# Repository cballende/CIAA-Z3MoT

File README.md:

# CIAA-Z3MoT
Simplificación de base board Silabs subGHz :
EZR32 Happy gecko board for QFP48 parts (EZR32HG)
[SLWSTK6244A](https://www.silabs.com/products/development-tools/wireless/proprietary/slwstk6244a-ezr32-happy-gecko-169-mhz-starter-kit)

| Kit        | Frequency(MHz)| Output Power(dBm) |Included Device |
| ------------- |:-------------:| -----:|-----:|
| SLWSTK6244A     | 169 | +20 | ZR32HG330FG63G |

#### Caracteristicas

* Adaptación de [CIAA-Z3R0](http://www.proyecto-ciaa.com.ar/devwiki/doku.php?id=desarrollo:ciaa-z3r0) hacia un enfoque de [MoTe](https://en.wikipedia.org/wiki/Sensor_node).

* Los pines entre Z3R0 y Z3MoT són compatibles en cierto grado, con excepción de los destinados a la interface RF.

* Puertos y pines deprecados de la versión Z3RO a la Z3MoT:
  - A:2,8,9,10. 
  - C:0,1,2,3,4. 

* Introduce 4 GPIO: 
Se utilizan 3 lineas para configurar puerto I2C para memoria EEPROM y posibles MEMs(disponibles V2.0,temperatura,humedad,7DOF,Altímetro-barómetro,luxómetro)

Deja un GPIO libre configurable sobre los restantes puertos:
- A:0,1.
- B:7,8,11,13,14.
- C:8,9,10,14,15.
- D:4,5,6,7.
- E:10,11,12,13.
- F:0,1,2,3,4.

* USB:
El conector usb se modifico, no se utiliza conector soldable. Se implemento un plug en pcb USB A troquelable, brindando la posiblidad soldar tira de pines de paso 1,27" o soldar en PCB tipo castellated.

* Alimentación:
Selección mediante jumper permitiendo conmutar bateria o (USB / PCBtarget).
La alimentación mediante bateria se implemento con fuente DC/DC tipo boost.

* Autonomía:
El stick Z3MoT tiene la posiblidad de usar baterias tipo boton CR2032(3V)(1,8 años autonomia 225 mAh) o mediante Pila AAA(7,25 años 1,5V de 900-1155 mAh). 

* Conectores RF:
Es posible utilizar dos tipos de conectores uno SMD(por defecto) y otro SMA(soldando via).

* JTAG:
Los pines utilizados en Z3RO son los mismos que para Z3MoT. Se adiciona tira de pines para conexión ordenada de JTAG  mediante sondas con resortes montadas sobre una pinza o base con balancin.

#### Schematic

[Schematic in pdf](ciaa-z3mot.pdf)

#### 3D view

## Vista con opciones de bateria y conector RF

## Video (YOUTUBE)

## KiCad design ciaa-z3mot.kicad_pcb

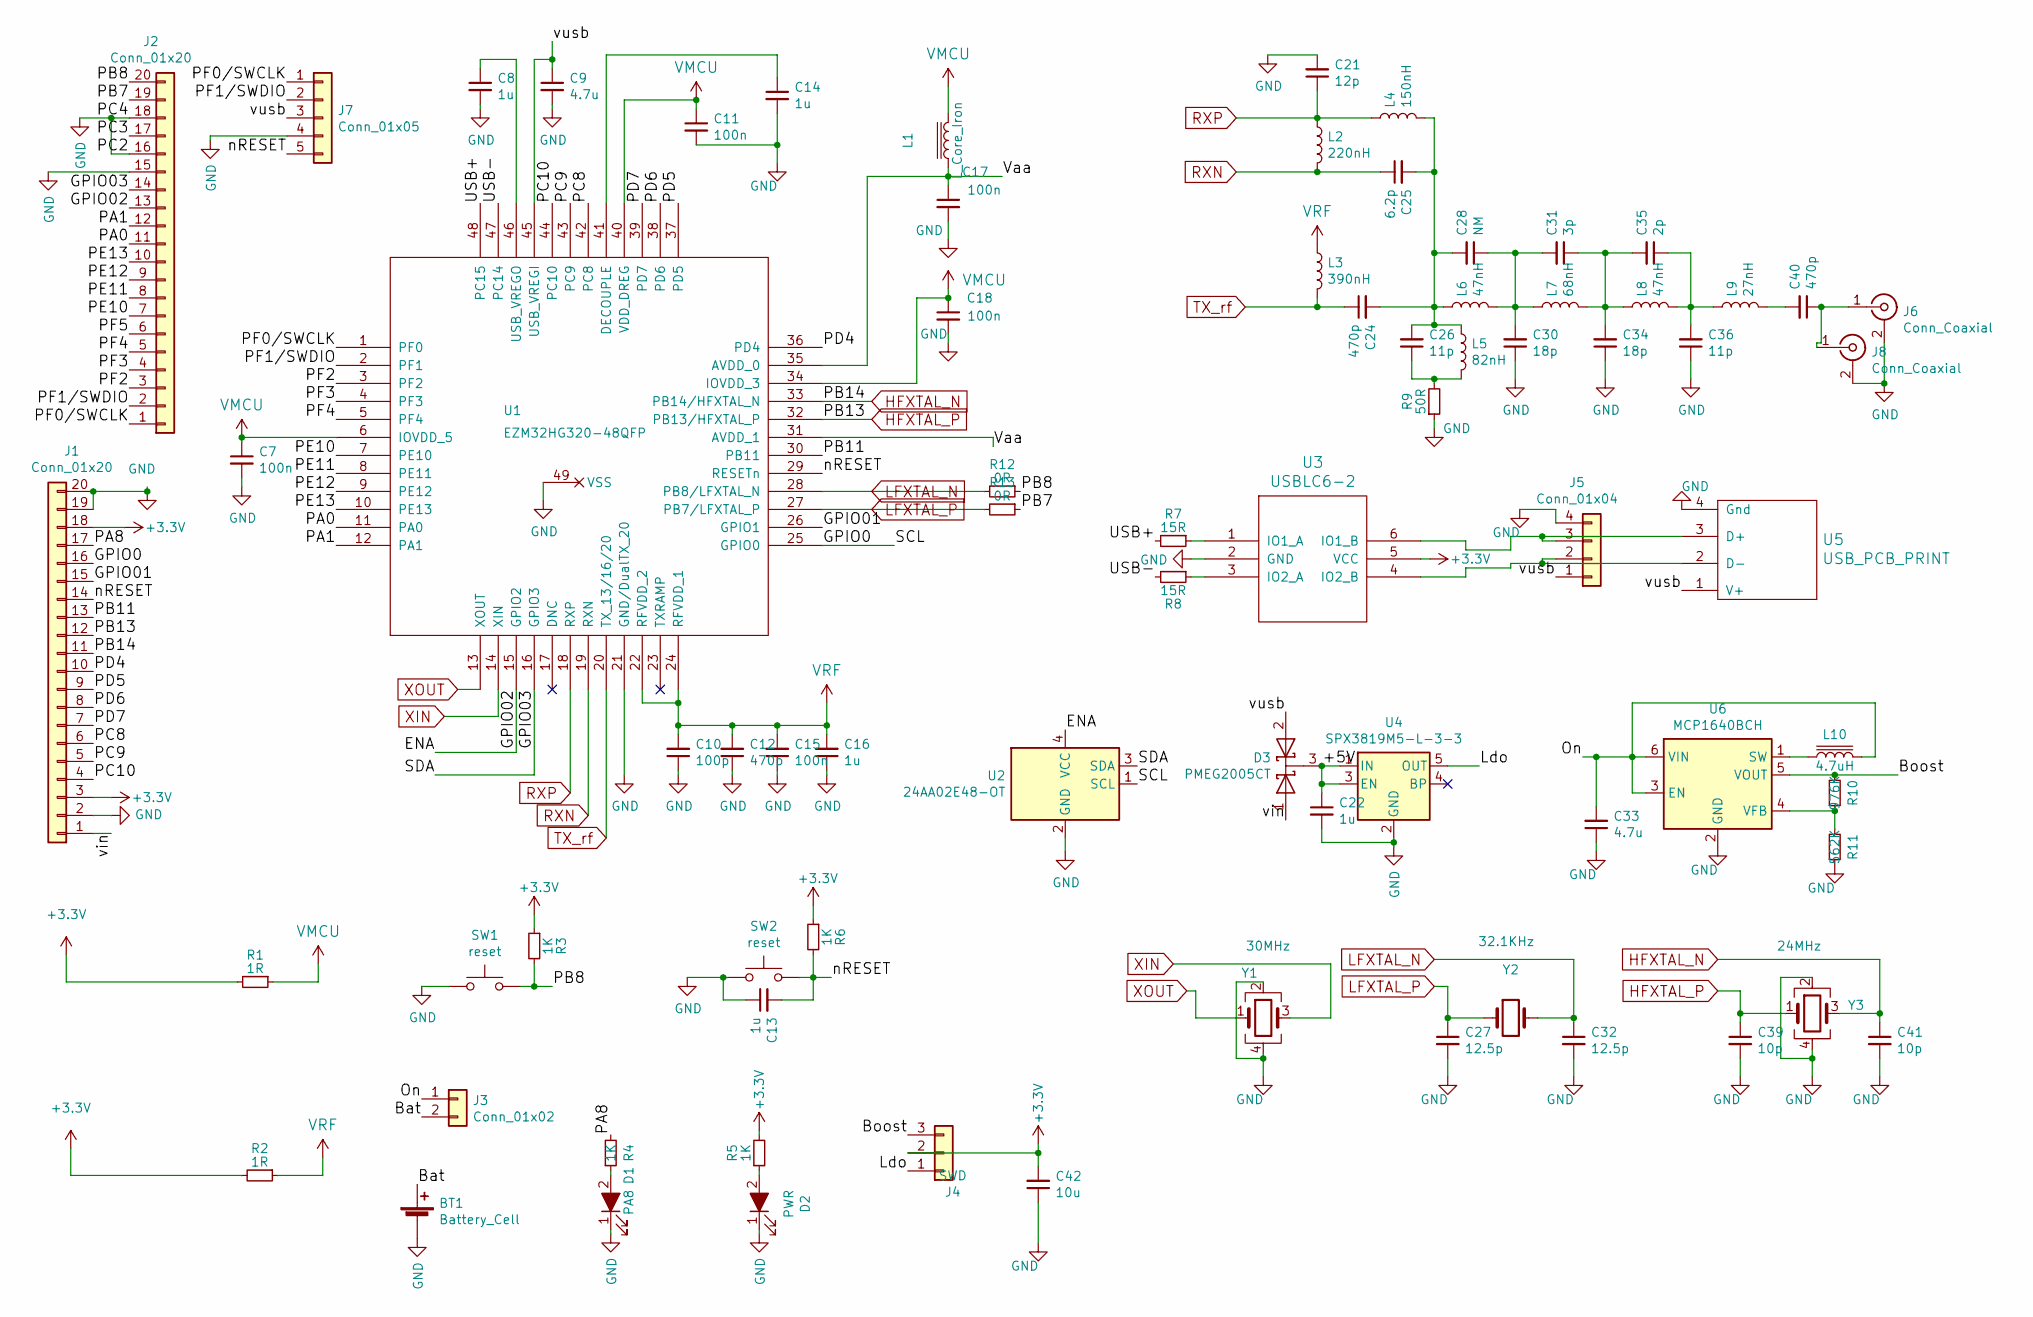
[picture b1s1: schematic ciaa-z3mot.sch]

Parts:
BT1: Battery_Cell; Battery_Panasonic_CR2032-VS1N_Vertical_CircularHoles
C7, C11, C15, C17, C18: 100n; C_0402_1005Metric
C8, C13, C22: 1u; C_0603_1608Metric
C9: 4.7u; C_0603_1608Metric
C10: 100p; C_0402_1005Metric
C12, C24, C40: 470p; C_0402_1005Metric
C14, C16: 1u; C_0402_1005Metric
C21: 12p; C_0402_1005Metric
C25: 6.2p; C_0402_1005Metric
C26, C36: 11p; C_0402_1005Metric
C27, C32: 12.5p; C_0402_1005Metric
C28: NM; C_0402_1005Metric
C30, C34: 18p; C_0402_1005Metric
C31: 3p; C_0402_1005Metric
C33: 4.7u; C_0805_2012Metric
C35: 2p; C_0402_1005Metric
C39, C41: 10p; C_0402_1005Metric
C42: 10u; C_1206_3216Metric
D1: PA8; LED_0805
D2: PWR; LED_0805
D3: PMEG2005CT; SOT-23
J1, J2: Conn_01x20; Pin_Header_Straight_1x20_Pitch2.54mm
J3: Conn_01x02; PinHeader_1x02_P1.27mm_Vertical
J4: SWD; PinHeader_1x03_P1.27mm_Vertical
J5: Conn_01x04; PinHeader_1x04_P1.27mm_Vertical
J6: Conn_Coaxial; SMA_Amphenol_132134-16_Vertical
J7: Conn_01x05; PinHeader_1x05_P1.27mm_Vertical
J8: Conn_Coaxial; U.FL_Hirose_U.FL-R-SMT-1_Vertical
L1: L_Core_Iron; L_0402_1005Metric
L2: 220nH; L_0402_1005Metric
L3: 390nH; L_0603_1608Metric
L4: 150nH; L_0402_1005Metric
L5: 82nH; L_0402_1005Metric
L6, L8: 47nH; L_0402_1005Metric
L7: 68nH; L_0402_1005Metric
L9: 27nH; L_0402_1005Metric
L10: 4.7uH; L_1008_2520Metric
R1, R2: 1R; R_0201_0603Metric
R3, R4, R5, R6: 1K; R_0402_1005Metric
R7, R8: 15R; R_0402_1005Metric
R9: 50R; R_0402_1005Metric
R10: 976K; R_0402_1005Metric
R11: 562K; R_0402_1005Metric
R12, R13: 0R; R_0201_0603Metric
SW1, SW2: reset; SW_SPST_B3U-1000P
U1: EZM32HG320-48QFP; QFN-48-1EP_7x7mm_P0.5mm_EP5.3x5.3mm
U2: 24AA02E48-OT; SOT-23-5
U3: USBLC6-2; SOT-23-6
U4: SPX3819M5-L-3-3; SOT-23-5
U5: USB_PCB_PRINT; USB_PCB_FOOTPRINT
U6: MCP1640BCH; SOT-23-6
Y1: 30MHz; Oscillator_SMD_Abracon_ASDMB-4Pin_2.5x2.0mm
Y2: 32.1KHz; Xtal_LF
Y3: 24MHz; Oscillator_SMD_Abracon_ASDMB-4Pin_2.5x2.0mm

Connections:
+3V3: C42.2, J1.3, J1.18, J4.2, R1.2, R2.2, R3.1, R5.2, R6.1, U3.5 (VCC); also elsewhere on the board
/+5V: C22.1, D3.3 (K), U4.1 (IN), U4.3 (EN)
/Bat: BT1.1 (+), J3.2
/Boost: J4.3, R10.2, U6.5 (VOUT)
/ENA: J2.13, U1.15 (GPIO2), U2.4 (VCC); also elsewhere on the board
/GPIO0: J1.16, U1.25 (GPIO0), U2.1 (SCL); also elsewhere on the board
/GPIO01: J1.15, U1.26 (GPIO1); also elsewhere on the board
/GPIO03: J2.14, U1.16 (GPIO3), U2.3 (SDA); also elsewhere on the board
/Ldo: J4.1, U4.5 (OUT)
/On: C33.2, J3.1, L10.2, U6.3 (EN), U6.6 (VIN)
/PA0: J2.11, U1.11 (PA0); also elsewhere on the board
/PA1: J2.12, U1.12 (PA1); also elsewhere on the board
/PA8: J1.17, R4.2; also elsewhere on the board
/PB7: J2.19, R13.1; also elsewhere on the board
/PB8: J2.20, R3.2, R12.1, SW1.2; also elsewhere on the board
/PB11: J1.13, U1.30 (PB11); also elsewhere on the board
/PC3: J2.17; also elsewhere on the board
/PC8: J1.6, U1.42 (PC8); also elsewhere on the board
/PC9: J1.5, U1.43 (PC9); also elsewhere on the board
/PC10: J1.4, U1.44 (PC10); also elsewhere on the board
/PD4: J1.10, U1.36 (PD4); also elsewhere on the board
/PD5: J1.9, U1.37 (PD5); also elsewhere on the board
/PD6: J1.8, U1.38 (PD6); also elsewhere on the board
/PD7: J1.7, U1.39 (PD7); also elsewhere on the board
/PE10: J2.7, U1.7 (PE10); also elsewhere on the board
/PE11: J2.8, U1.8 (PE11); also elsewhere on the board
/PE12: J2.9, U1.9 (PE12); also elsewhere on the board
/PE13: J2.10, U1.10 (PE13); also elsewhere on the board
/PF0/SWCLK: J2.1, J7.1, U1.1 (PF0); also elsewhere on the board
/PF1/SWDIO: J2.2, J7.2, U1.2 (PF1); also elsewhere on the board
/PF2: J2.3, U1.3 (PF2); also elsewhere on the board
/PF3: J2.4, U1.4 (PF3); also elsewhere on the board
/PF4: J2.5, U1.5 (PF4); also elsewhere on the board
/PF5: J2.6; also elsewhere on the board
/USB+: R7.2, U1.48 (PC15)
/USB-: R8.2, U1.47 (PC14)
/Vaa: C17.1, L1.1, U1.31 (AVDD_1), U1.35 (AVDD_0)
/nRESET: C13.2, J1.14, J7.5, R6.2, SW2.2, U1.29 (RESETn); also elsewhere on the board
/vin: D3.1 (A), J1.1; also elsewhere on the board
/vusb: C9.1, D3.2 (A), J5.1, J7.3, U1.45 (USB_VREGI), U5.1 (V+)
GND: BT1.2 (-), C7.2, C8.2, C9.2, C10.1, C11.2, C12.1, C13.1, C14.2, C15.1, C16.1, C17.2, C18.2, C21.2, C22.2, C27.2, C30.1, C32.2, C33.1, C34.1, C36.1, C39.2, C41.2, C42.1, D1.1 (K), D2.1 (K), J1.2, J1.19, J1.20, J2.15, J2.16, J2.18, J5.4, J6.2 (Ext), J7.4, J8.2 (Ext), R9.1, R11.1, SW1.1, SW2.1, U1.21 (GND/DualTX_20), U1.49 (VSS), U2.2 (GND), U3.2 (GND), U4.2 (GND), U5.4 (Gnd), U6.2 (GND), Y1.2, Y1.4, Y3.2, Y3.4; also elsewhere on the board
HFXTAL_N: C41.1, J1.11, U1.33 (PB14/HFXTAL_N), Y3.3; also elsewhere on the board
HFXTAL_P: C39.1, J1.12, U1.32 (PB13/HFXTAL_P), Y3.1; also elsewhere on the board
LFXTAL_N: C32.1, R12.2, U1.28 (PB8/LFXTAL_N), Y2.2
LFXTAL_P: C27.1, R13.2, U1.27 (PB7/LFXTAL_P), Y2.1
unnamed: C8.1, U1.46 (USB_VREGO)
unnamed: C14.1, U1.41 (DECOUPLE)
unnamed: C24.2, C25.2, C26.2, C28.2, L4.2, L5.1, L6.1
unnamed: C26.1, L5.2, R9.2
unnamed: C28.1, C30.2, C31.2, L6.2, L7.1
unnamed: C31.1, C34.2, C35.2, L7.2, L8.1
unnamed: C35.1, C36.2, L8.2, L9.1
unnamed: C40.1, J6.1 (In), J8.1 (In)
unnamed: C40.2, L9.2
unnamed: D1.2 (A), R4.1
unnamed: D2.2 (A), R5.1
unnamed: J5.2, U3.4 (IO2_B), U5.2 (D-)
unnamed: J5.3, U3.6 (IO1_B), U5.3 (D+)
unnamed: L10.1, U6.1 (SW)
unnamed: R7.1, U3.1 (IO1_A)
unnamed: R8.1, U3.3 (IO2_A)
unnamed: R10.1, R11.2, U6.4 (VFB)
RXN: C25.1, L2.2, U1.19 (RXN)
RXP: C21.1, L2.1, L4.1, U1.18 (RXP)
TX_rf: C24.1, L3.2, U1.20 (TX_13/16/20)
VMCU: C7.1, C11.1, C18.1, L1.2, R1.1, U1.6 (IOVDD_5), U1.34 (IOVDD_3), U1.40 (VDD_DREG)
VRF: C10.2, C12.2, C15.2, C16.2, L3.1, R2.1, U1.22 (RFVDD_2), U1.24 (RFVDD_1)
XIN: U1.14 (XIN), Y1.3
XOUT: U1.13 (XOUT), Y1.1

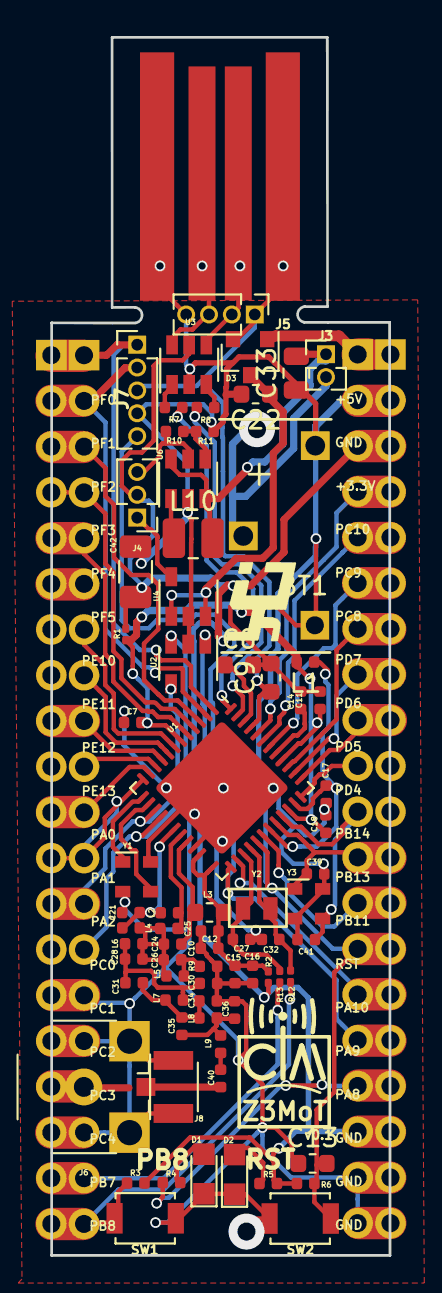
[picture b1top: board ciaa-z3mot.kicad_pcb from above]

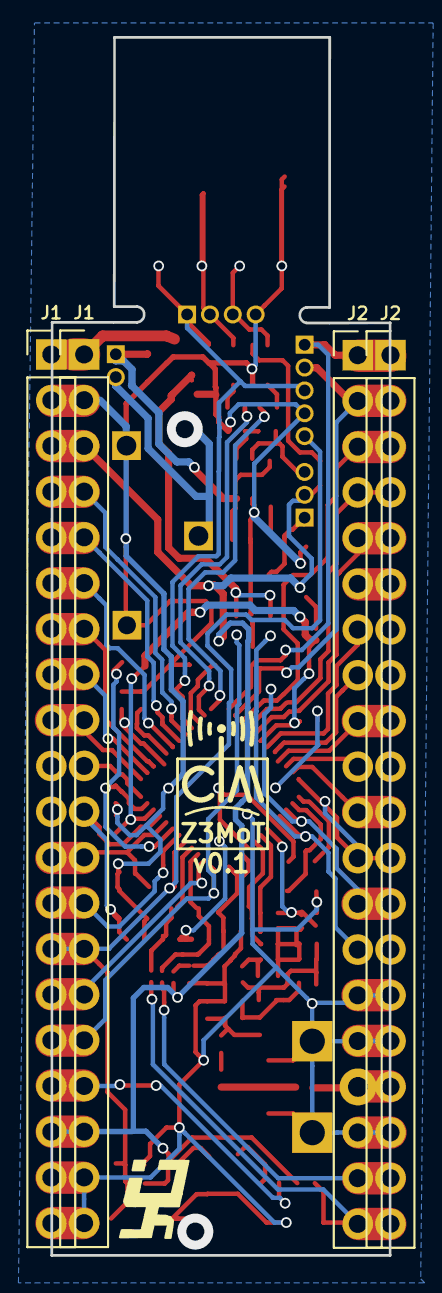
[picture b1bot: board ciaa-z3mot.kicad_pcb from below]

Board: 2 copper layers, 18.8 x 67.7 mm, 78 parts (4 on the bottom side), 69 nets.

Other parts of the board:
J1#2, J2#2: Conn_01x20; Pin_Header_Straight_1x20_Pitch2.54mm

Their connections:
+3V3: J1#2.3, J1#2.18; also elsewhere on the board
/ENA: J2#2.13; also elsewhere on the board
/GPIO0: J1#2.16; also elsewhere on the board
/GPIO01: J1#2.15; also elsewhere on the board
/GPIO03: J2#2.14; also elsewhere on the board
/PA0: J2#2.11; also elsewhere on the board
/PA1: J2#2.12; also elsewhere on the board
/PA8: J1#2.17; also elsewhere on the board
/PB7: J2#2.19; also elsewhere on the board
/PB8: J2#2.20; also elsewhere on the board
/PB11: J1#2.13; also elsewhere on the board
/PC3: J2#2.17; also elsewhere on the board
/PC8: J1#2.6; also elsewhere on the board
/PC9: J1#2.5; also elsewhere on the board
/PC10: J1#2.4; also elsewhere on the board
/PD4: J1#2.10; also elsewhere on the board
/PD5: J1#2.9; also elsewhere on the board
/PD6: J1#2.8; also elsewhere on the board
/PD7: J1#2.7; also elsewhere on the board
/PE10: J2#2.7; also elsewhere on the board
/PE11: J2#2.8; also elsewhere on the board
/PE12: J2#2.9; also elsewhere on the board
/PE13: J2#2.10; also elsewhere on the board
/PF0/SWCLK: J2#2.1; also elsewhere on the board
/PF1/SWDIO: J2#2.2; also elsewhere on the board
/PF2: J2#2.3; also elsewhere on the board
/PF3: J2#2.4; also elsewhere on the board
/PF4: J2#2.5; also elsewhere on the board
/PF5: J2#2.6; also elsewhere on the board
/nRESET: J1#2.14; also elsewhere on the board
/vin: J1#2.1; also elsewhere on the board
GND: J1#2.2, J1#2.19, J1#2.20, J2#2.15, J2#2.16, J2#2.18; also elsewhere on the board
HFXTAL_N: J1#2.11; also elsewhere on the board
HFXTAL_P: J1#2.12; also elsewhere on the board

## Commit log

2019-09-30 Init
2019-10-01 mejoras 1
2019-10-02 sin verificar ruteo gnd
2019-10-03 render completo y cambio smd pack
2019-10-03 agrego porta baterias
2019-10-03 implementación con opciones
2019-10-04 Edición readme
2019-10-04 more readme!!! ):
2020-03-06 BOM
    edicion de fb mdp1640 y en el bom
2021-05-01 rectifico

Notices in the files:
ciaa-z3mot.sch:
Copyright © by Sebastián Allende
